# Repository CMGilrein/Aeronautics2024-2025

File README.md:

# Aeronautics2024-2025
The code for embedded systems used within the deployed glider for the 2024-2025 school year FAA DBF competition

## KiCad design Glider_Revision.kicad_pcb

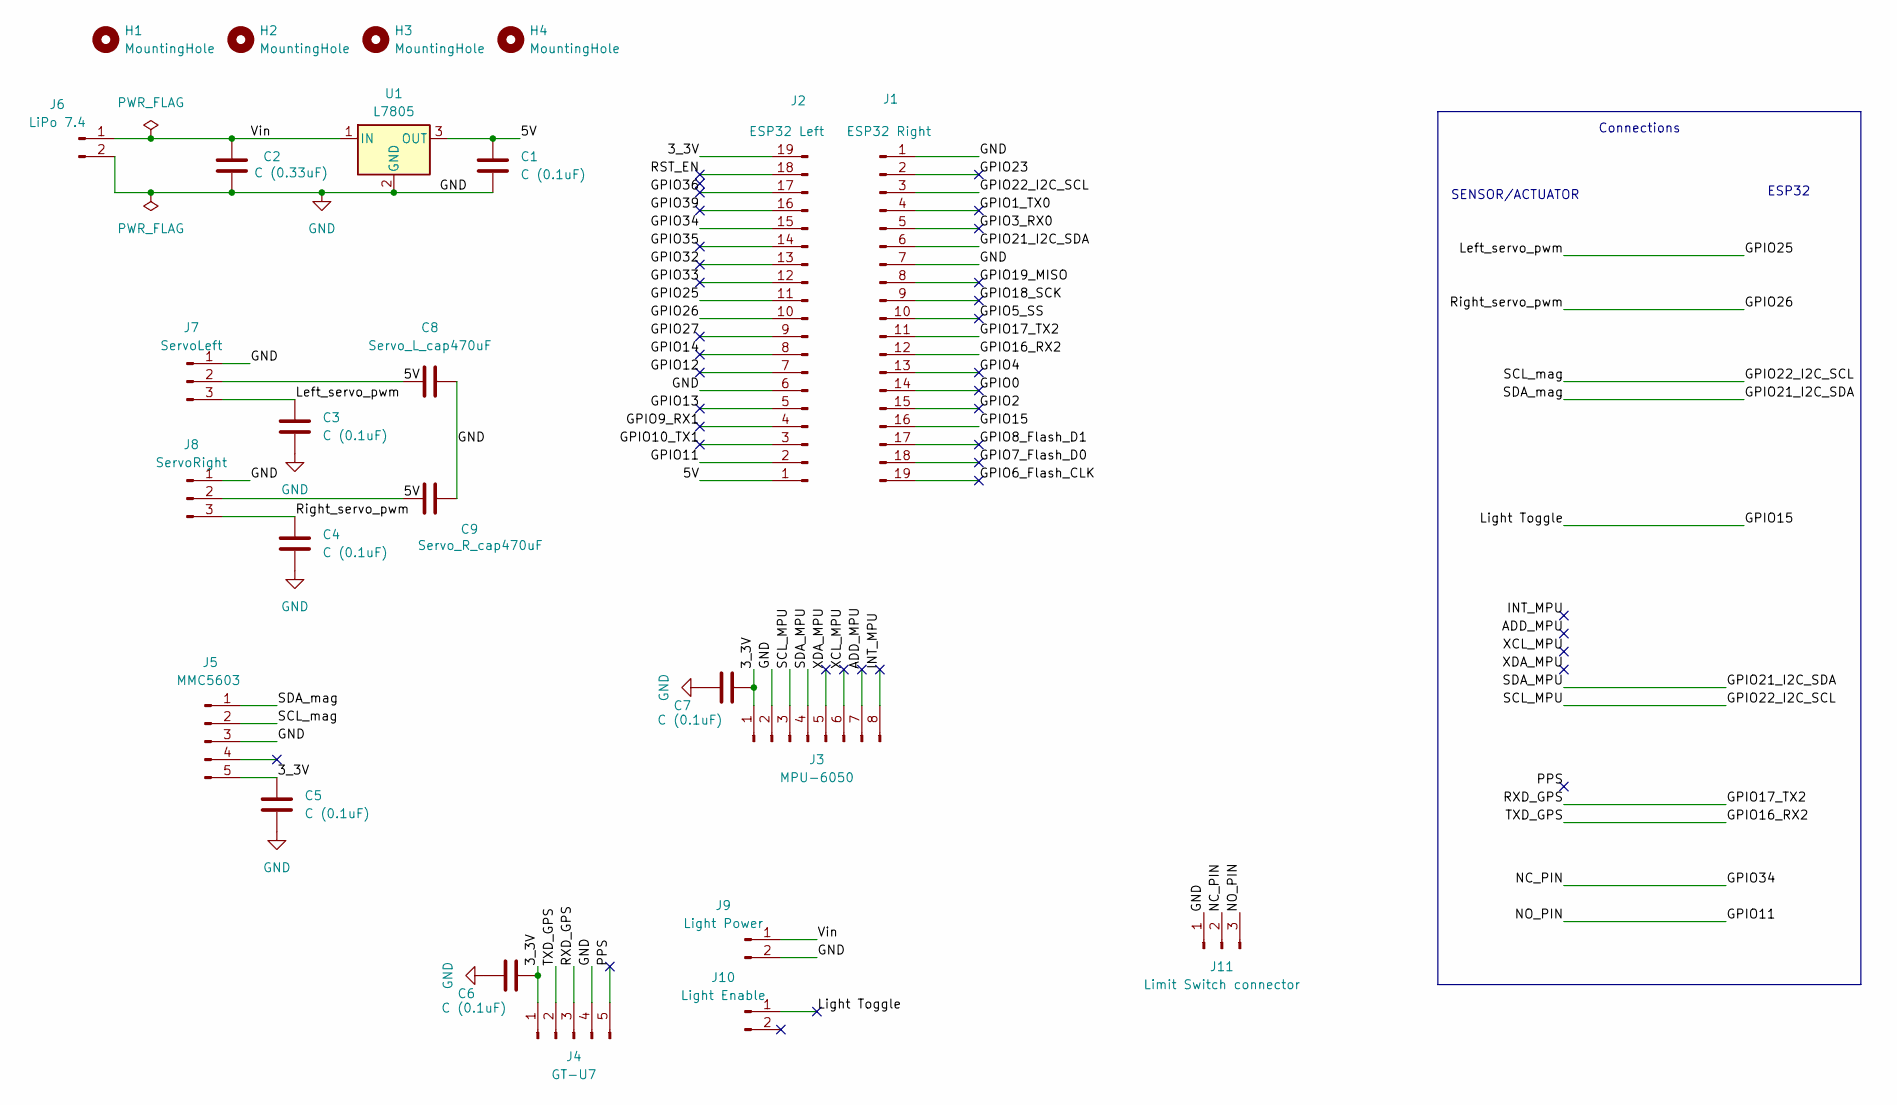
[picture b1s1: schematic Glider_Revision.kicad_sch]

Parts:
C1, C3, C4, C5, C6, C7: C (0.1uF); CP_Radial_D4.0mm_P2.00mm
C2: C (0.33uF); CP_Radial_D4.0mm_P2.00mm
C8: Servo_L_cap470uF; CP_Radial_D4.0mm_P2.00mm
C9: Servo_R_cap470uF; CP_Radial_D4.0mm_P2.00mm
H1, H2, H3, H4: MountingHole; MountingHole_2.5mm_Pad
J1: ESP32 Right; PinHeader_1x19_P2.54mm_Vertical
J2: ESP32 Left; PinHeader_1x19_P2.54mm_Vertical
J3: MPU-6050; PinHeader_1x08_P2.54mm_Vertical
J4: GT-U7; PinHeader_1x05_P2.54mm_Vertical
J5: MMC5603; PinHeader_1x05_P2.54mm_Vertical
J6: LiPo 7.4; PinSocket_1x02_P2.54mm_Vertical
J7: ServoLeft; PinHeader_1x03_P2.54mm_Vertical
J8: ServoRight; PinHeader_1x03_P2.54mm_Vertical
J9: Light Power; PinHeader_1x02_P2.54mm_Vertical
J10: Light Enable; PinHeader_1x02_P2.54mm_Vertical
J11: Limit Switch connector; PinHeader_1x03_P2.54mm_Vertical
U1: L7805; TO-220-3_Vertical

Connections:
/3_3V: C5.1, C6.1, C7.1, J2.19, J3.1, J4.1, J5.5
/5V: C1.1, C8.1, C9.1, J2.1, J7.2, J8.2, U1.3 (OUT)
/ADD_MPU: J3.7
/GPIO0: J1.14
/GPIO1_TX0: J1.4
/GPIO2: J1.15
/GPIO3_RX0: J1.5
/GPIO4: J1.13
/GPIO5_SS: J1.10
/GPIO6_Flash_CLK: J1.19
/GPIO7_Flash_D0: J1.18
/GPIO8_Flash_D1: J1.17
/GPIO9_RX1: J2.4
/GPIO10_TX1: J2.3
/GPIO11: J2.2, J11.3
/GPIO12: J2.7
/GPIO13: J2.5
/GPIO14: J2.8
/GPIO15: J1.16, J10.1
/GPIO16_RX2: J1.12, J4.2
/GPIO17_TX2: J1.11, J4.3
/GPIO18_SCK: J1.9
/GPIO19_MISO: J1.8
/GPIO21_I2C_SDA: J1.6, J3.4, J5.1
/GPIO22_I2C_SCL: J1.3, J3.3, J5.2
/GPIO23: J1.2
/GPIO25: C3.1, J2.11, J7.3
/GPIO26: C4.1, J2.10, J8.3
/GPIO27: J2.9
/GPIO32: J2.13
/GPIO33: J2.12
/GPIO34: J2.15, J11.2
/GPIO35: J2.14
/GPIO36: J2.17
/GPIO39: J2.16
/INT_MPU: J3.8
/PPS: J4.5
/RST_EN: J2.18
/Vin: C2.1, J6.1, J9.1, U1.1 (IN)
/XCL_MPU: J3.6
/XDA_MPU: J3.5
GND: C1.2, C2.2, C3.2, C4.2, C5.2, C6.2, C7.2, C8.2, C9.2, J1.1, J1.7, J2.6, J3.2, J4.4, J5.3, J6.2, J7.1, J8.1, J9.2, J11.1, U1.2 (GND)

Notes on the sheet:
Connections
ESP32
SENSOR/ACTUATOR

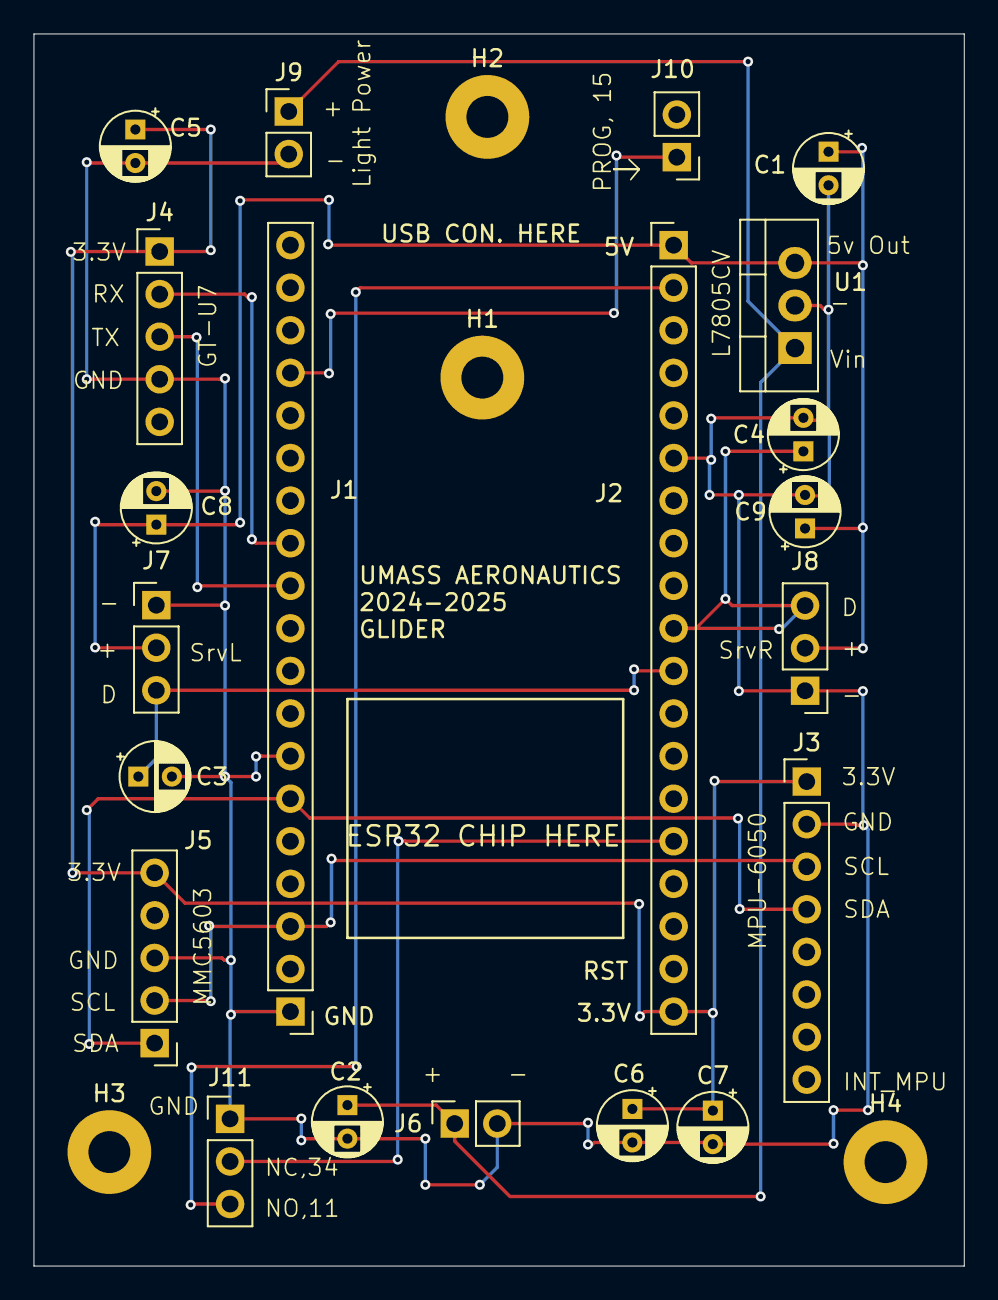
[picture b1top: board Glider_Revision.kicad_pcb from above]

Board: 2 copper layers, 55.5 x 73.5 mm, 25 parts (0 on the bottom side), 13 nets.

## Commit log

2024-12-13 Code
2025-02-16 stuff
2025-02-17 Schemnatic updates
